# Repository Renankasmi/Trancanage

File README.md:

# Trancanage Treuil Frema

Ce projet propose une nouvelle version durcie du système de trancanage développé par et pour l'AACM (Association Aéronautique de Coulommiers Meaux)

Les visuels et dossier d'industrialisation proposés ici ne représente qu'une partie du système global et plus particulièrement la partie régulation et pilotage des moteurs électriques. 

## Les éléments du design

Le système est composé d'une partie moteur-commande et d'un capteur magnétique déporté. Une partie assemblage mécanique permettant de mettre en mouvement les bras de guidage n'est pas traitée dans le cadre de ce dépot GIT.

### Le capteur magnétique

Le capteur magnétique permet de compter le nombre de tours de la bobine du treuil Frema. Un aimant est directement collé sur la transmission et passe devant le capteur à chaque tour. L'information est ensuite renvoyée au boitier moteur commande pour calculer et ajuster la régulation (position et vitesse).

### Le boitier moteur-commande
La partie puissance composée d'un moteur électrique, d'un réducteur et d'une électronique associée est reliée au capteur magnétique.
Le boitier est directement collé sur le motoréducteur grâce à une pièce d'adaptation dont les plans sont disponibles dans ce dépôt.
A l'intérieur du boitier deux cartes électroniques se partagent le travail.  
Une __carte commande__ avec un microcontrôleur PIC, une interface RS232 et un capteur de position de l'axe moteur.
Une __carte de puissance__ avec un demi pont à base de transistor MOSFET, la generation des alimentations auxiliaires et des mesures courant/tensions.

## License

**Les travaux présentés ici sont sous la licence [Creative Commons Share-alike 4.0 International](http://creativecommons.org/licenses/by-sa/4.0/).**

Note : Il s'agit d'un résumé lisible par l'homme (et non d'un substitut) de [license](http://creativecommons.org/licenses/by-sa/4.0/legalcode).

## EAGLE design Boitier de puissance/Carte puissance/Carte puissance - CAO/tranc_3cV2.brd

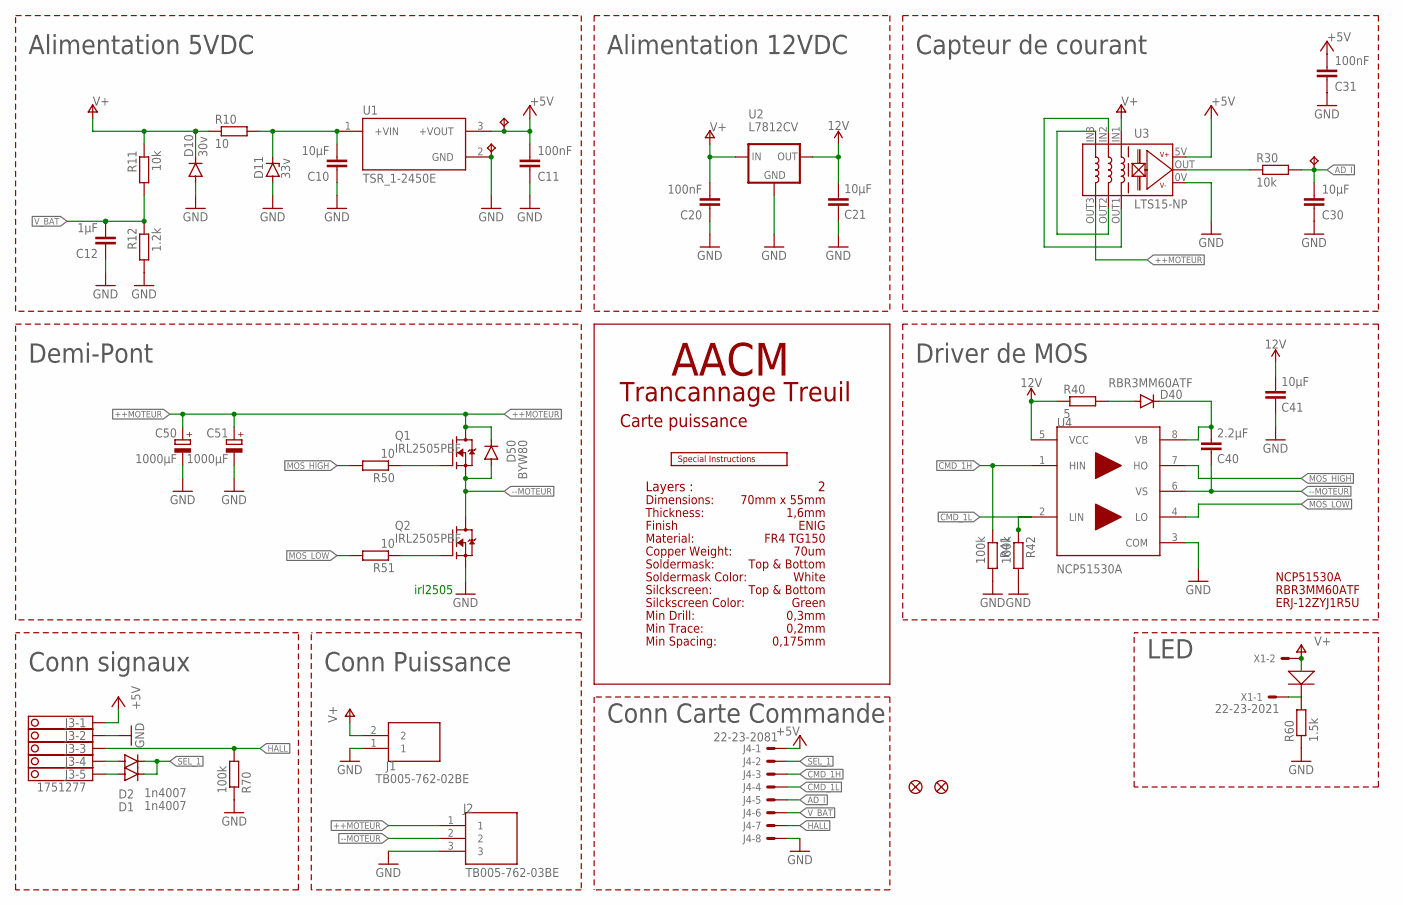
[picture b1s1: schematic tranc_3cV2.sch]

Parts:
5V: TPB1,27; B1,27
AD_I: TPB1,27; B1,27
C10, C21, C30, C41: 10µF; C1210
C11, C20, C31: 100nF; C0603
C12: 1µF; C0805
C40: 2.2µF; C1206
C50, C51: 1000µF; E7,5-18
D1, D2: 1n4007; SOD80C
D10: 30v; DO214AA
D11: 33v; SMB
D40: RBR3MM60ATF; SOD123
D50: BYW80; TO220ACS
FD1, FD2: FIDUCIAL1X2; FIDUCIAL-1X2
GND: TPB1,27; B1,27
J1: TB005-762-02BE; CUI_TB005-762-02BE
J2: TB005-762-03BE; CUI_TB005-762-03BE
J3: 1751277
J4: 22-23-2081
Q1, Q2: IRL2505PBF; TO220UPDOWN
R10: 10; R2512
R11, R30: 10k; R0603
R12: 1.2k; R0603
R40: 5; R2010
R41, R42: 100k; R0805
R50, R51: 10; R0805
R60: 1.5k; R0603
R70: 100k; R0603
U1: TSR_1-2450E; CONV_TSR_1-2450E
U2: L7812CV; 78XXS
U3: LTS15-NP
U4: NCP51530A; SOIC127P610X420-8N
U$1: SPECIAL_INSTRUCTIONS-PRODUCTION; PRODUCTION_INSTRUCTIONS
X1: 22-23-2021

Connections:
12V: C21.1, C41.1, R40.1, U2.OUT, U4.5 (VCC)
+5V: 5V.TP, C11.2, C31.2, J3.1, J4.1, U1.3 (+VOUT), U3.5V (V+)
++MOTEUR: C50.+, C51.+, D50.C, J2.1, Q1.2 (D), U3.OUT3
--MOTEUR: C40.2, D50.A, J2.2, Q1.3 (S), Q2.2 (D), U4.6 (VS)
AD_I: AD_I.TP, C30.2, J4.5, R30.2
BOOTSTRAP: D40.A, R40.2
CMD_1H: J4.3, R41.1, U4.1 (HIN)
CMD_1L: J4.4, R42.1, U4.2 (LIN)
GND: C10.1, C11.1, C12.1, C20.1, C21.2, C30.1, C31.1, C41.2, C50.-, C51.-, D10.A, D11.A, GND.TP, J1.1, J2.3, J3.2, J4.8, Q2.3 (S), R12.2, R41.2, R42.2, R60.1, R70.1, U1.2 (GND), U2.GND, U3.0V, U4.3 (COM)
HALL: J3.3, J4.7, R70.2
LED_K: R60.2, X1.1
MOS_HIGH: R50.2, U4.7 (HO)
MOS_HIGH_GATE: Q1.1 (G), R50.1
MOS_LOW: R51.2, U4.4 (LO)
MOS_LOW_GATE: Q2.1 (G), R51.1
SEL_1: D1.C, D2.C, J4.2
SENSOR_OUT: R30.1, U3.OUT (VOUT)
SPIRE1: U3.IN2, U3.OUT1
SPIRE2: U3.IN3, U3.OUT2
TSR_IN: C10.2, D11.C, R10.2, U1.1 (+VIN)
V+: C20.2, D10.C, J1.2, R10.1, R11.1, U2.IN, U3.IN1, X1.2
VB: C40.1, D40.C, U4.8 (VB)
V_BAT: C12.2, J4.6, R11.2, R12.1
X3-1: D1.A, J3.5
X3-2: D2.A, J3.4

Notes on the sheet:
irl2505
Alimentation 5VDC
Alimentation 12VDC
Capteur de courant
Driver de MOS
Demi-Pont
Conn signaux
Conn Puissance
LED
AACM
Trancannage Treuil
Carte puissance
Layers :
Dimensions:
Thickness:
Finish
Material:
Copper Weight:
Soldermask:
Soldermask Color:
Silckscreen:
Silckscreen Color:
Min Drill:
Min Trace:
Min Spacing:
70mm x 55mm
1,6mm
ENIG
FR4 TG150
70um
Top & Bottom
White
Green
0,3mm
0,2mm
0,175mm
Conn Carte Commande
RBR3MM60ATF
NCP51530A
ERJ-12ZYJ1R5U

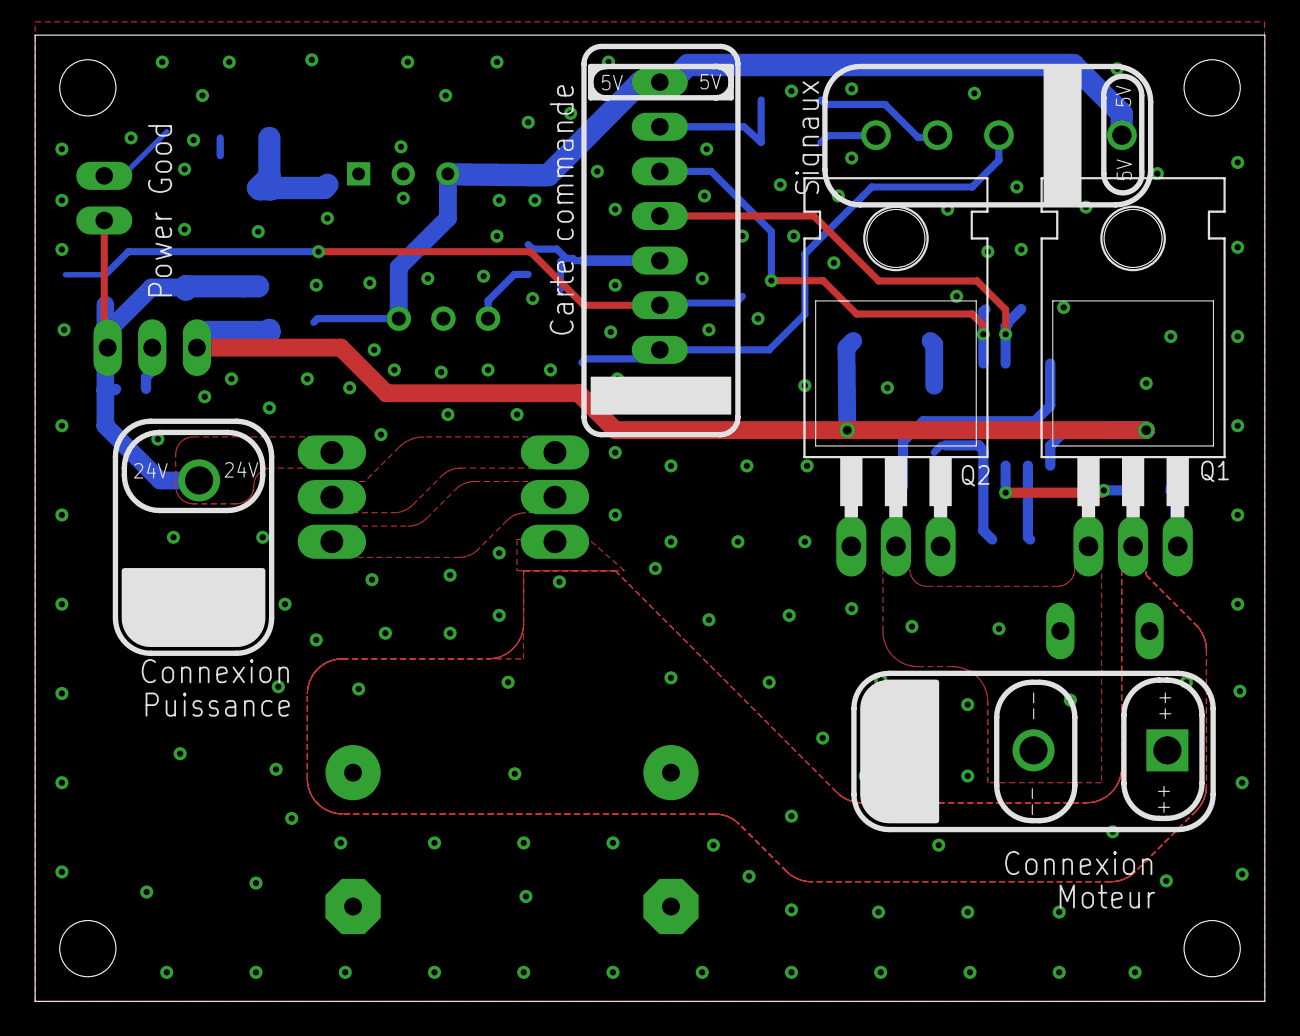
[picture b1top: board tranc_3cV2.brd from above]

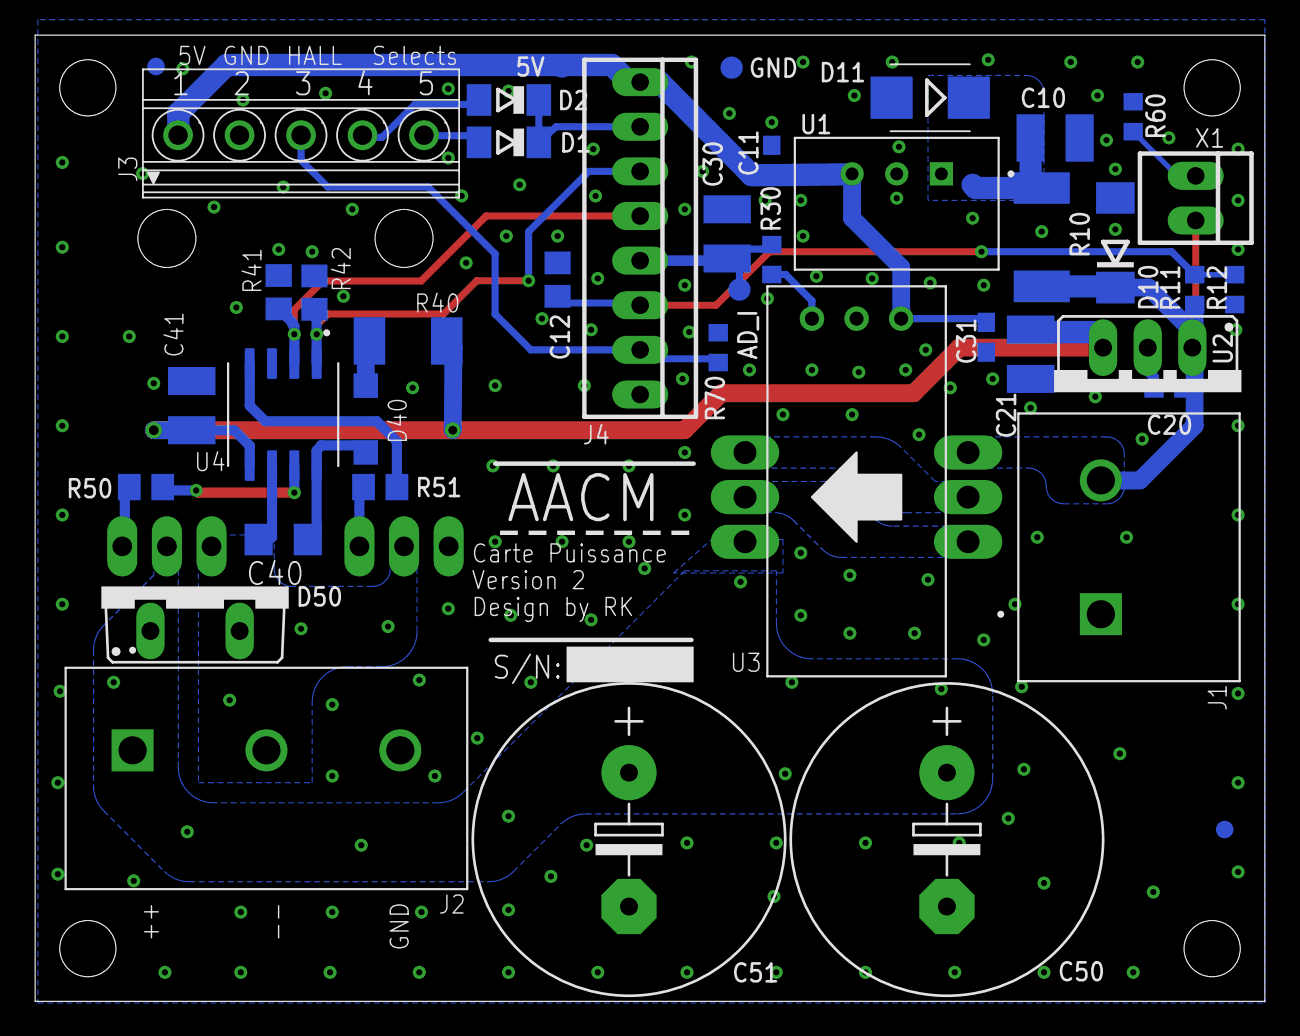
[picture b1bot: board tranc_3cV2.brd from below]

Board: 2 copper layers, 70.0 x 55.0 mm, 45 parts (42 on the bottom side), 25 nets.

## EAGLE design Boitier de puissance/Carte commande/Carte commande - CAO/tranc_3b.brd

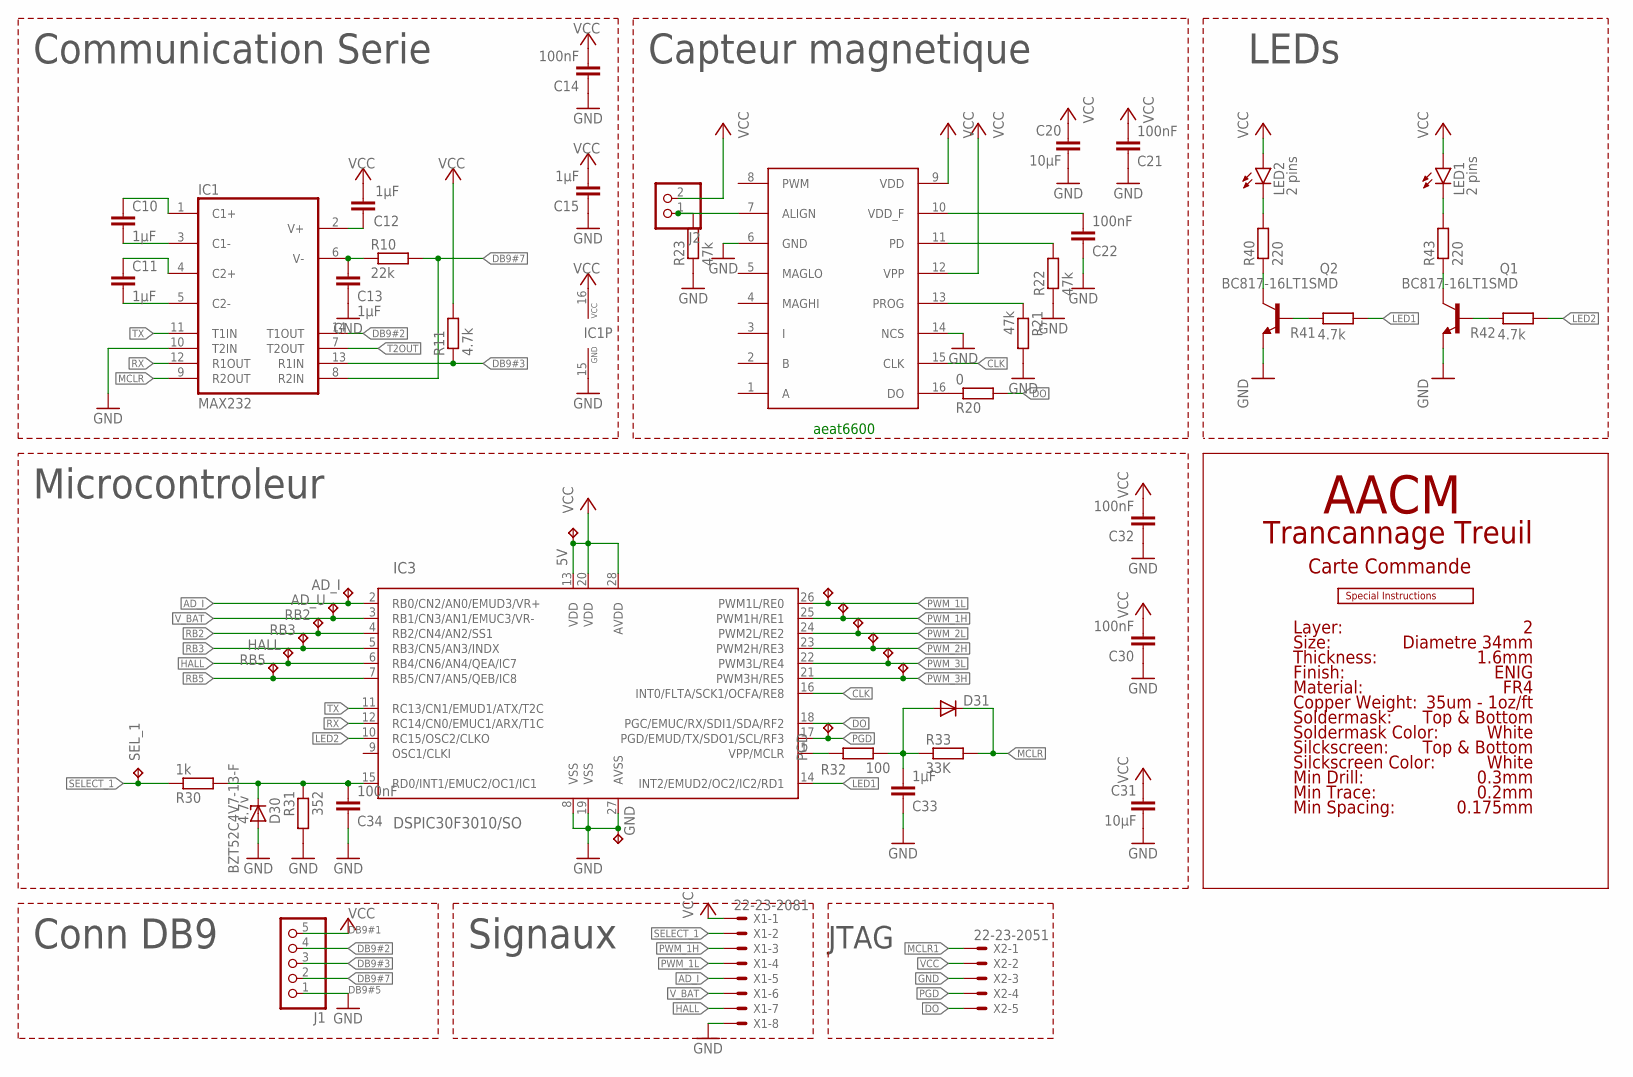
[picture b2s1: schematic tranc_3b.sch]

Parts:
1H, 1L, 2H, 2L, 3H, 3L, 5V: TPB1,27; B1,27
AD_I: TPB1,27; B1,27
AD_U: TPB1,27; B1,27
C10, C11, C12, C13, C15, C33: 1µF; C0603
C14, C21, C22, C30, C32, C34: 100nF; C0603
C20, C31: 10µF; C1210
D30: 4.7v; SOD80C
D31: DIODE-MINIMELF; MINIMELF
GND: TPB1,27; B1,27
HALL: TPB1,27; B1,27
IC1: MAX232; SO16
IC2: AVAGO_AEAT-6600TSSOP16; AVAGO_TSSOP16
IC3: DSPIC30F3010/SO; SO-28W
J1: PINHD-1X55X2MM; 1_05X2MM
J2: PINHD-1X2; 1X02
LED1, LED2: 2 pins; LED3MM
PGD: TPB1,27; B1,27
Q1, Q2: BC817-16LT1SMD; SOT23-BEC
R10: 22k; R0603
R11, R41, R42: 4.7k; R0603
R20: 0; R0603
R21, R22, R23: 47k; R0603
R30: 1k; R0603
R31: 352; R0603
R32: 100; R0603
R33: 33K; R0603
R40, R43: 220; R0603
RB2, RB3, RB5: TPB1,27; B1,27
SEL_1: TPB1,27; B1,27
U$1: SPECIAL_INSTRUCTIONS-PRODUCTION; PRODUCTION_INSTRUCTIONS
X1: 22-23-2081
X2: 22-23-2051

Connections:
AD_I: AD_I.TP, IC3.2 (RB0/CN2/AN0/EMUD3/VR+), X1.5
ALIGN: IC2.7 (ALIGN), J2.1, R23.2
BASEL1: Q1.C, R43.1
BASEL2: Q2.C, R40.1
C1+: C10.1, IC1.1 (C1+)
C1-: C10.2, IC1.3 (C1-)
C2+: C11.1, IC1.4 (C2+)
C2-: C11.2, IC1.5 (C2-)
CLK: IC2.15 (CLK), IC3.16 (INT0/FLTA/SCK1/OCFA/RE8)
DB9#2: IC1.14 (T1OUT), J1.4
DB9#3: IC1.13 (R1IN), J1.3, R11.1
DB9#7: IC1.8 (R2IN), J1.2, R10.2
DO: IC3.18 (PGC/EMUC/RX/SDI1/SDA/RF2), R20.2, X2.5
DO_1: IC2.16 (DO), R20.1
GND: C13.2, C14.1, C15.1, C20.2, C21.1, C22.1, C30.1, C31.2, C32.1, C33.1, C34.1, D30.A, GND.TP, IC1.10 (T2IN), IC1.15 (GND), IC2.6 (GND), IC2.14 (NCS), IC3.8 (VSS), IC3.19 (VSS), IC3.27 (AVSS), J1.1, Q1.E, Q2.E, R21.2, R22.1, R23.1, R31.2, X1.8, X2.3
HALL: HALL.TP, IC3.6 (RB4/CN6/AN4/QEA/IC7), X1.7
KL1: LED1.K (C), R43.2
KL2: LED2.K (C), R40.2
LED1: IC3.14 (INT2/EMUD2/OC2/IC2/RD1), R41.1
LED1GATE: Q2.B, R41.2
LED2: IC3.10 (RC15/OSC2/CLKO), R42.1
LED2GATE: Q1.B, R42.2
MCLR: D31.C, IC1.9 (R2OUT), R33.2
MCLR1: IC3.1 (VPP/MCLR), R32.1, X2.1
MCLR2: C33.2, D31.A, R32.2, R33.1
PGD: IC3.17 (PGD/EMUD/TX/SDO1/SCL/RF3), PGD.TP, X2.4
POWERDOWN: IC2.11 (PD), R22.2
PROG: IC2.13 (PROG), R21.1
PWM_1H: 1H.TP, IC3.25 (PWM1H/RE1), X1.3
PWM_1L: 1L.TP, IC3.26 (PWM1L/RE0), X1.4
PWM_2H: 2H.TP, IC3.23 (PWM2H/RE3)
PWM_2L: 2L.TP, IC3.24 (PWM2L/RE2)
PWM_3H: 3H.TP, IC3.21 (PWM3H/RE5)
PWM_3L: 3L.TP, IC3.22 (PWM3L/RE4)
RB2: IC3.4 (RB2/CN4/AN2/SS1), RB2.TP
RB3: IC3.5 (RB3/CN5/AN3/INDX), RB3.TP
RB5: IC3.7 (RB5/CN7/AN5/QEB/IC8), RB5.TP
RX: IC1.12 (R1OUT), IC3.12 (RC14/CN0/EMUC1/ARX/T1C)
SELECT: C34.2, D30.C, IC3.15 (RD0/INT1/EMUC2/OC1/IC1), R30.2, R31.1
SELECT_1: R30.1, SEL_1.TP, X1.2
T2OUT: IC1.7 (T2OUT)
TX: IC1.11 (T1IN), IC3.11 (RC13/CN1/EMUD1/ATX/T2C)
V+232: C12.1, IC1.2 (V+)
V-232: C13.1, IC1.6 (V-), R10.1
VCC: 5V.TP, C12.2, C14.2, C15.2, C20.1, C21.2, C30.2, C31.1, C32.2, IC1.16 (VCC), IC2.9 (VDD), IC2.12 (VPP), IC3.13 (VDD), IC3.20 (VDD), IC3.28 (AVDD), J1.5, J2.2, LED1.A, LED2.A, R11.2, X1.1, X2.2
VDD_F: C22.2, IC2.10 (VDD_F)
V_BAT: AD_U.TP, IC3.3 (RB1/CN3/AN1/EMUC3/VR-), X1.6

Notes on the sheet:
aeat6600
DB9#5
DB9#1
Communication Serie
Capteur magnetique
LEDs
Microcontroleur
Conn DB9
Signaux
AACM
Trancannage Treuil
Carte Commande
JTAG
Layer:
Size:
Thickness:
Finish:
Copper Weight:
Material:
Soldermask:
Soldermask Color:
Silckscreen:
Silckscreen Color:
Min Drill:
Min Trace:
Min Spacing:
Diametre 34mm
1.6mm
ENIG
35um - 1oz/ft
FR4
Top & Bottom
White
0.3mm
0.2mm
0.175mm

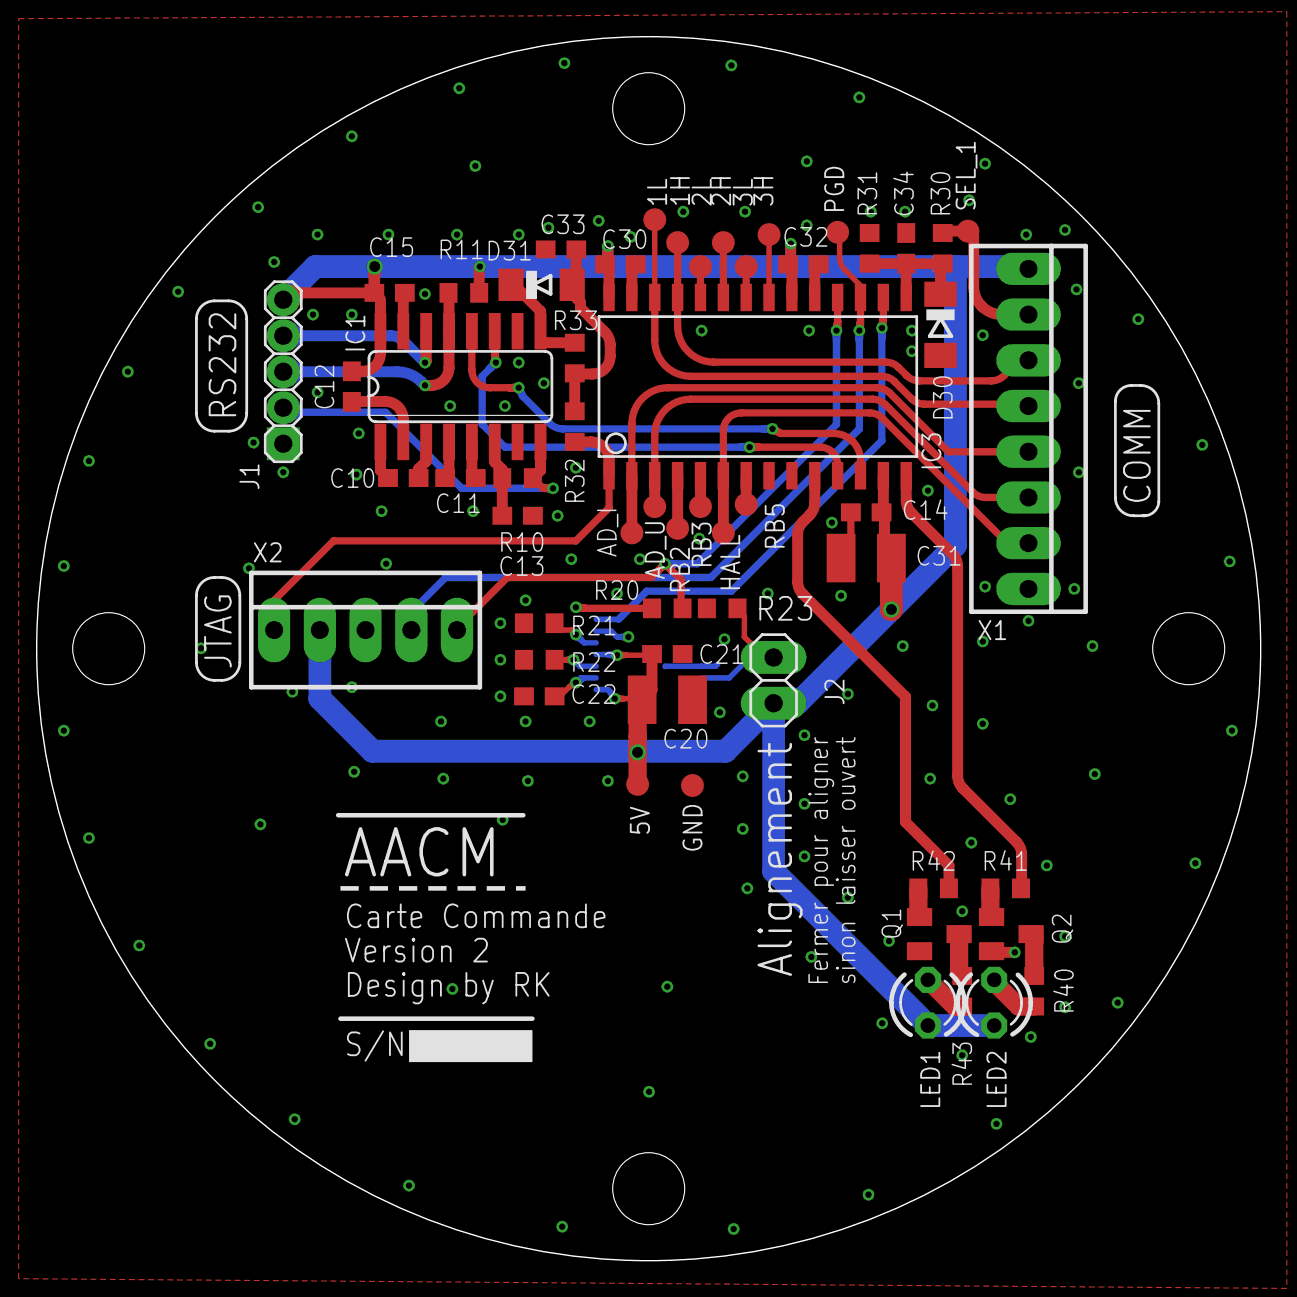
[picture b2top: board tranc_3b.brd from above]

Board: 2 copper layers, 68.0 x 68.0 mm, 58 parts (1 on the bottom side), 46 nets.

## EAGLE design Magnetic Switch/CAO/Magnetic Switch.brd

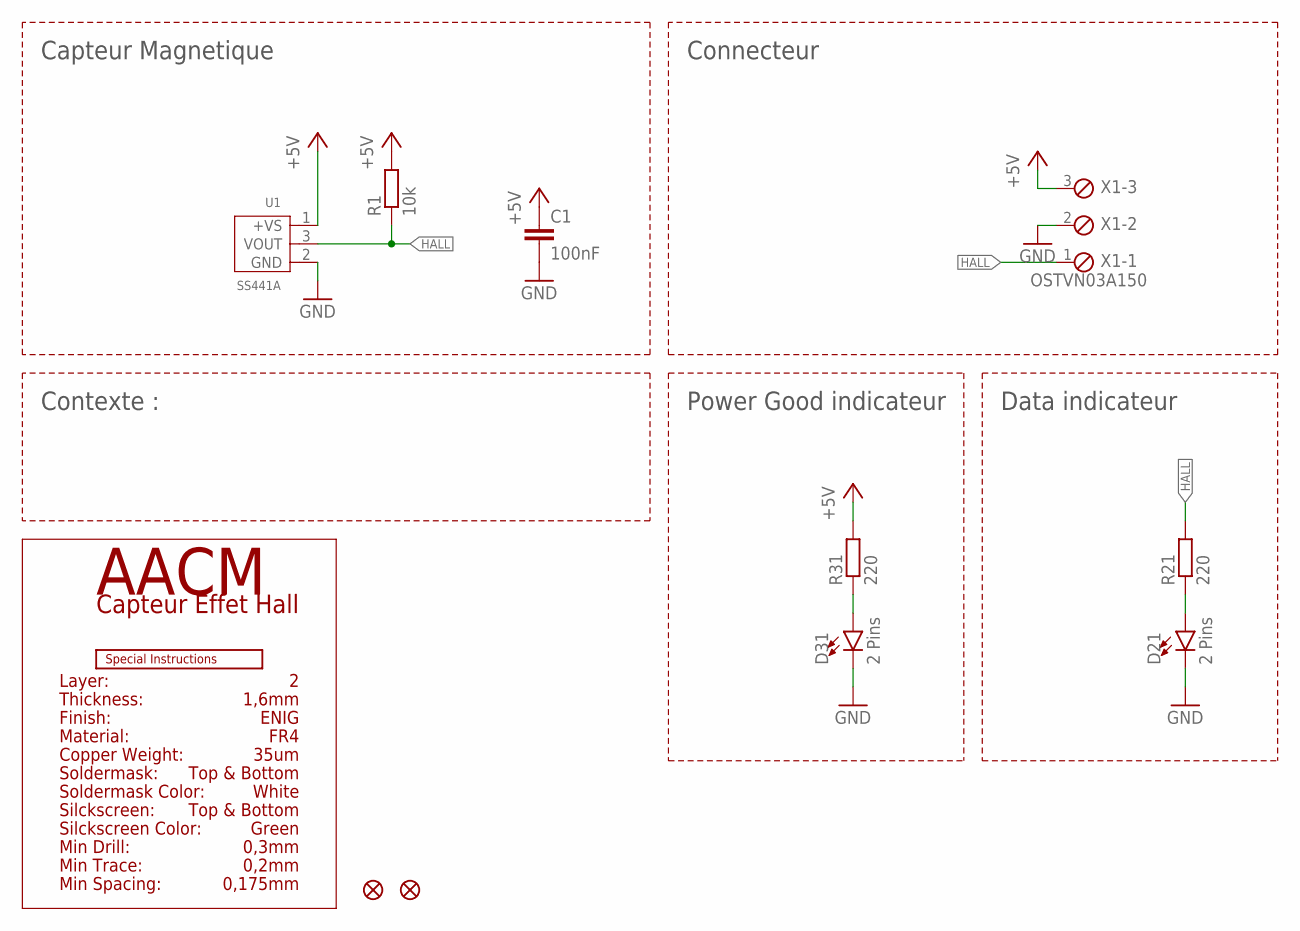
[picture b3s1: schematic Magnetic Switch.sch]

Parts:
C1: 100nF; C0603
D21, D31: 2 Pins; LED_3MM
FD1, FD2: FIDUCIALUFIDUCIAL; FIDUCIAL-MICRO
R1: 10k; R0603
R21, R31: 220; R0603
U1: SS441A; TO-92-3
U$1: SPECIAL_INSTRUCTIONS-PRODUCTION; PRODUCTION_INSTRUCTIONS
X1: OSTVN03A150; 3POL254

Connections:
+5V: C1.1, R1.2, R31.2, U1.1 (+VS), X1.3
DIODED21: D21.A, R21.1
DIODED31: D31.A, R31.1
GND: C1.2, D21.K (C), D31.K (C), U1.2 (GND), X1.2
HALL: R1.1, R21.2, U1.3 (VOUT), X1.1

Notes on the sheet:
Capteur Magnetique
Connecteur
Power Good indicateur
Data indicateur
Contexte :
Thickness:
Finish:
Material:
Copper Weight:
Soldermask:
Soldermask Color:
Silckscreen Color:
Silckscreen:
Min Drill:
Min Trace:
Min Spacing:
Layer:
0,2mm
0,3mm
Green
Top & Bottom
White
FR4
35um
ENIG
1,6mm
0,175mm
AACM
Capteur Effet Hall

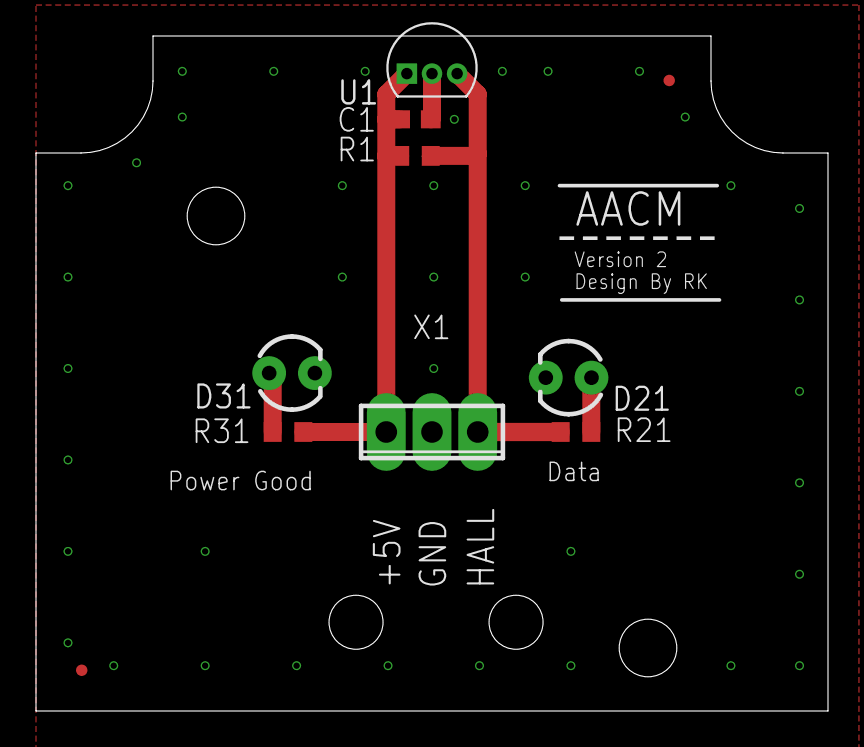
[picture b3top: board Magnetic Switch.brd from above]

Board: 2 copper layers, 44.0 x 37.5 mm, 11 parts (0 on the bottom side), 5 nets.

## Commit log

2023-01-03 Ajout des fichiers du capteur magnétique
2023-01-03 Ajout des données du boitier de puissance
2023-01-15 Ajout des fichiers pour la carte commande et la carte puissance
2023-01-15 Création d'un fichier Readme.md
2023-01-16 Ajout du détail des cartes
2023-01-16 Ajout des plans boitier et radiateur
2023-01-17 Ajout archive

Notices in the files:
parts and their libraries:
SparkFun-Aesthetics: Licensing: Creative Commons ShareAlike 4.0 International - https://creativecommons.org/licenses/by-sa/4.0
